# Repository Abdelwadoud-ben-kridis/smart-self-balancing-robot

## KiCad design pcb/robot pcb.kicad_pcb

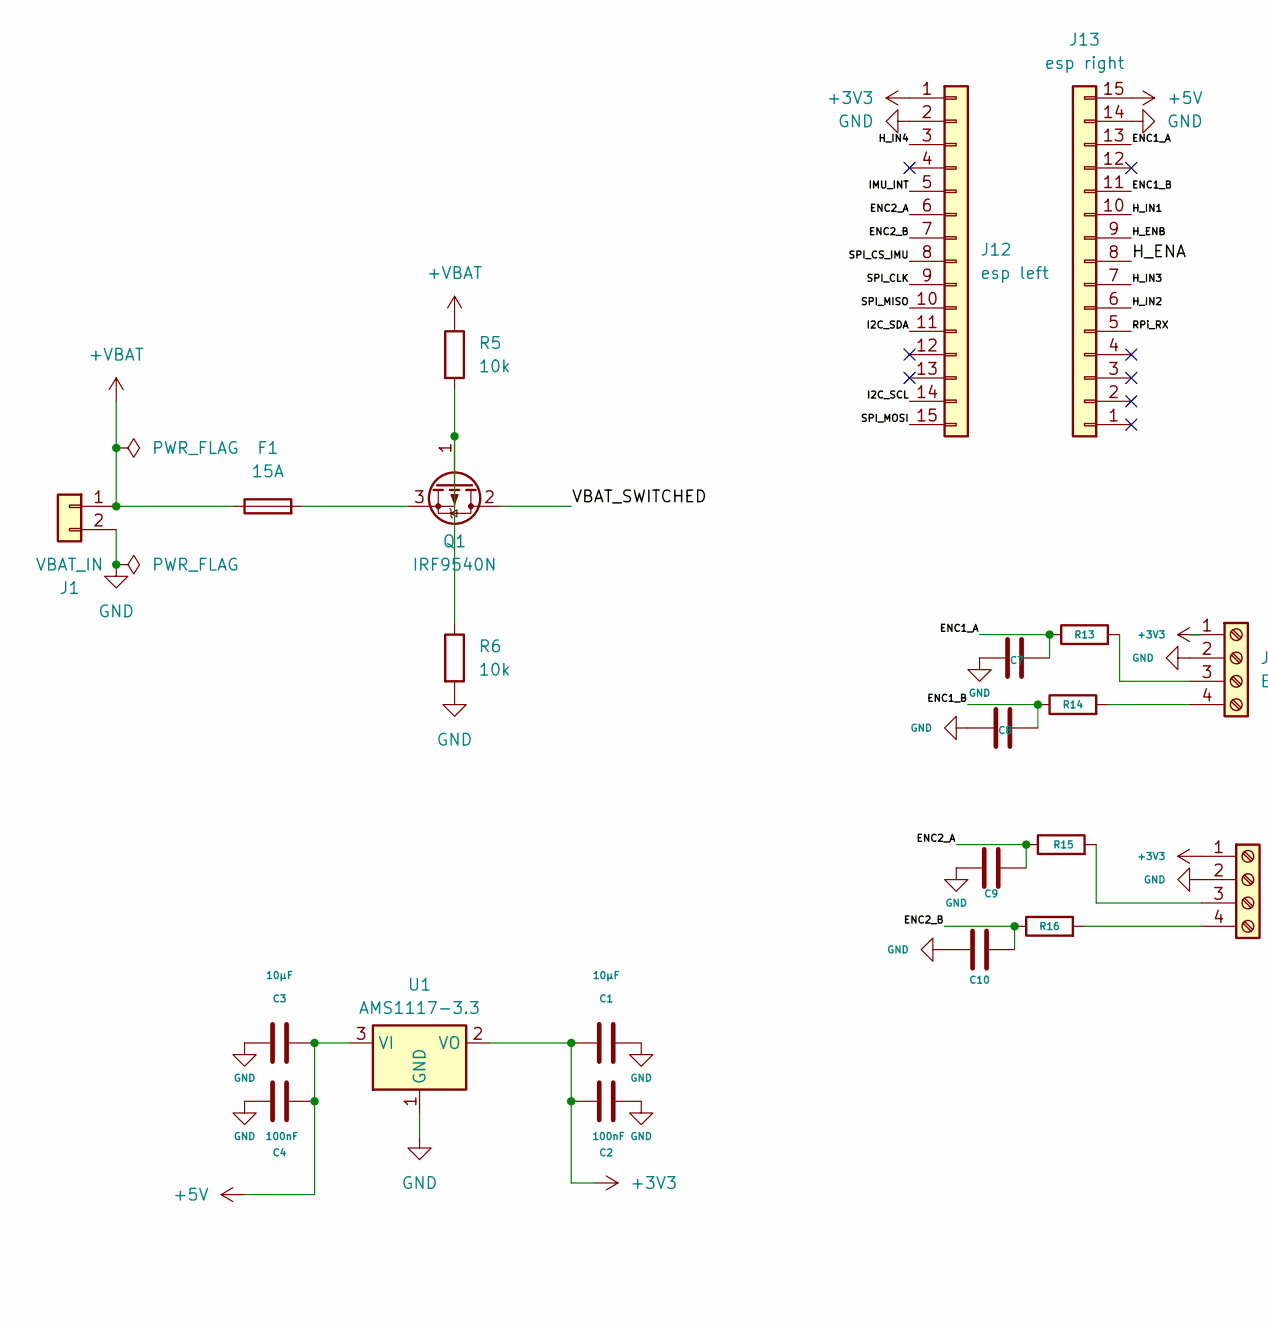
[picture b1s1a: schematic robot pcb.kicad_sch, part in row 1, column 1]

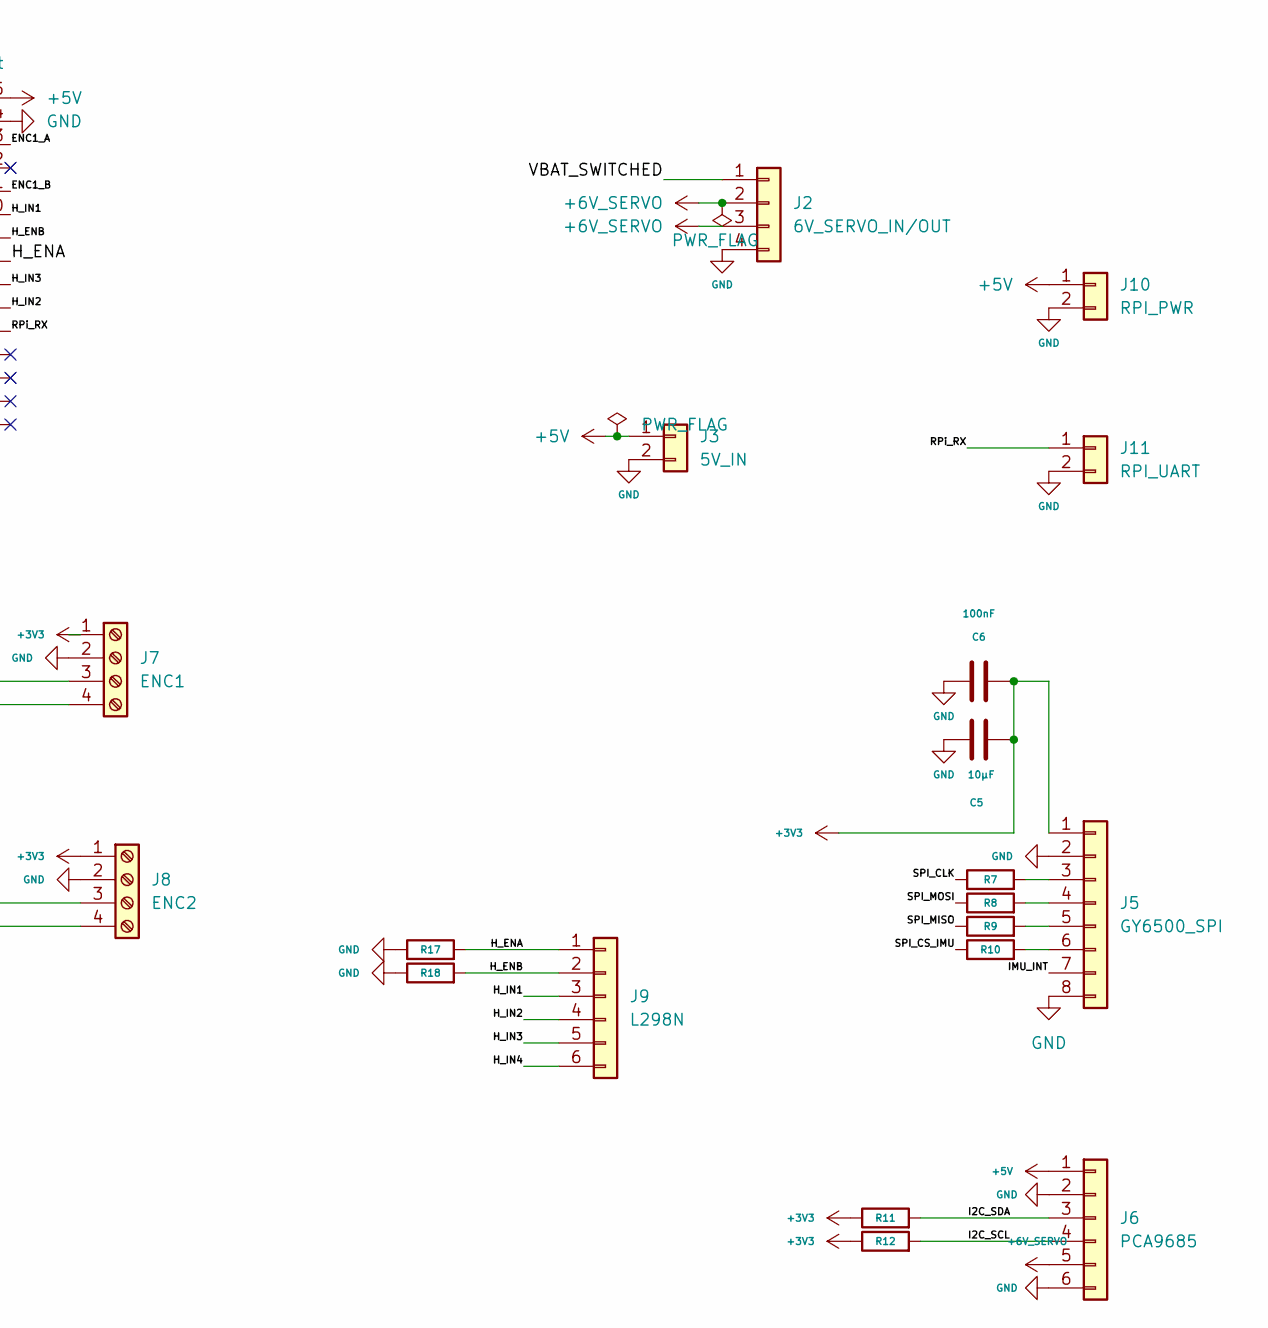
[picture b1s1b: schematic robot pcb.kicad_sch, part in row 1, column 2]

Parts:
C1, C3, C5: 10µF; CP_Radial_D5.0mm_P2.50mm
C2, C4, C6: 100nF; C_Disc_D3.8mm_W2.6mm_P2.50mm
C7, C8, C9, C10: C; C_Disc_D3.8mm_W2.6mm_P2.50mm
F1: 15A; Fuseholder_Cylinder-5x20mm_Schurter_FPG4_Vertical_Closed
J1: VBAT_IN; PinHeader_1x02_P2.54mm_Vertical
J2: 6V_SERVO_IN/OUT; PinHeader_1x04_P2.54mm_Vertical
J3: 5V_IN; PinHeader_1x02_P2.54mm_Vertical
J5: GY6500_SPI; PinHeader_1x08_P2.54mm_Vertical
J6: PCA9685; PinHeader_1x06_P2.54mm_Vertical
J7: ENC1; TerminalBlock_MaiXu_MX126-5.0-04P_1x04_P5.00mm
J8: ENC2; TerminalBlock_MaiXu_MX126-5.0-04P_1x04_P5.00mm
J9: L298N; PinHeader_1x06_P2.54mm_Vertical
J10: RPI_PWR; PinHeader_1x02_P2.54mm_Vertical
J11: RPI_UART; PinHeader_1x02_P2.54mm_Vertical
J12: esp left; PinSocket_1x15_P2.54mm_Vertical
J13: esp right; PinSocket_1x15_P2.54mm_Vertical
Q1: IRF9540N; TO-220-3_Vertical
R5, R6: 10k; R_Axial_DIN0207_L6.3mm_D2.5mm_P10.16mm_Horizontal
R7, R8, R9, R10: 33; R_Axial_DIN0207_L6.3mm_D2.5mm_P10.16mm_Horizontal
R11, R12: 4.7k; R_Axial_DIN0207_L6.3mm_D2.5mm_P10.16mm_Horizontal
R13, R14, R15, R16: 1k; R_Axial_DIN0207_L6.3mm_D2.5mm_P10.16mm_Horizontal
R17, R18: 10kΩ; R_Axial_DIN0207_L6.3mm_D2.5mm_P10.16mm_Horizontal
U1: AMS1117-3.3; SOT-223-3_TabPin2

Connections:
+3V3: C1.2, C2.2, C5.1, C6.1, J5.1, J7.1, J8.1, J12.1, R11.1, R12.1, U1.2 (VO)
+5V: C3.1, C4.1, J3.1, J6.1, J10.1, J13.15, U1.3 (VI)
+6V_SERVO: J2.2, J2.3, J6.5
+VBAT: F1.1, J1.1, R5.1
/ENC1_A: C7.2, J13.13, R13.1
/ENC1_B: C8.2, J13.11, R14.1
/ENC2_A: C9.2, J12.6, R15.1
/ENC2_B: C10.2, J12.7, R16.1
/H_ENA: J9.1, J13.8, R17.2
/H_ENB: J9.2, J13.9, R18.2
/H_IN1: J9.3, J13.10
/H_IN2: J9.4, J13.6
/H_IN3: J9.5, J13.7
/H_IN4: J9.6, J12.3
/I2C_SCL: J6.4, J12.14, R12.2
/I2C_SDA: J6.3, J12.11, R11.2
/IMU_INT: J5.7, J12.5
/RPi_RX: J11.1, J13.5
/SPI_CLK: J12.9, R7.1
/SPI_CS_IMU: J12.8, R10.1
/SPI_MISO: J12.10, R9.1
/SPI_MOSI: J12.15, R8.1
/VBAT_SWITCHED: J2.1, Q1.2 (D)
GND: C1.1, C2.1, C3.2, C4.2, C5.2, C6.2, C7.1, C8.1, C9.1, C10.1, J1.2, J2.4, J3.2, J5.2, J5.8, J6.2, J6.6, J7.2, J8.2, J10.2, J11.2, J12.2, J13.14, R6.2, R17.1, R18.1, U1.1 (GND)
unnamed: J5.3, R7.2
unnamed: J5.4, R8.2
unnamed: J5.5, R9.2
unnamed: J5.6, R10.2
unnamed: J7.3, R13.2
unnamed: J7.4, R14.2
unnamed: J8.3, R15.2
unnamed: J8.4, R16.2
unnamed: Q1.1 (G), R5.2, R6.1
unnamed: F1.2, Q1.3 (S)

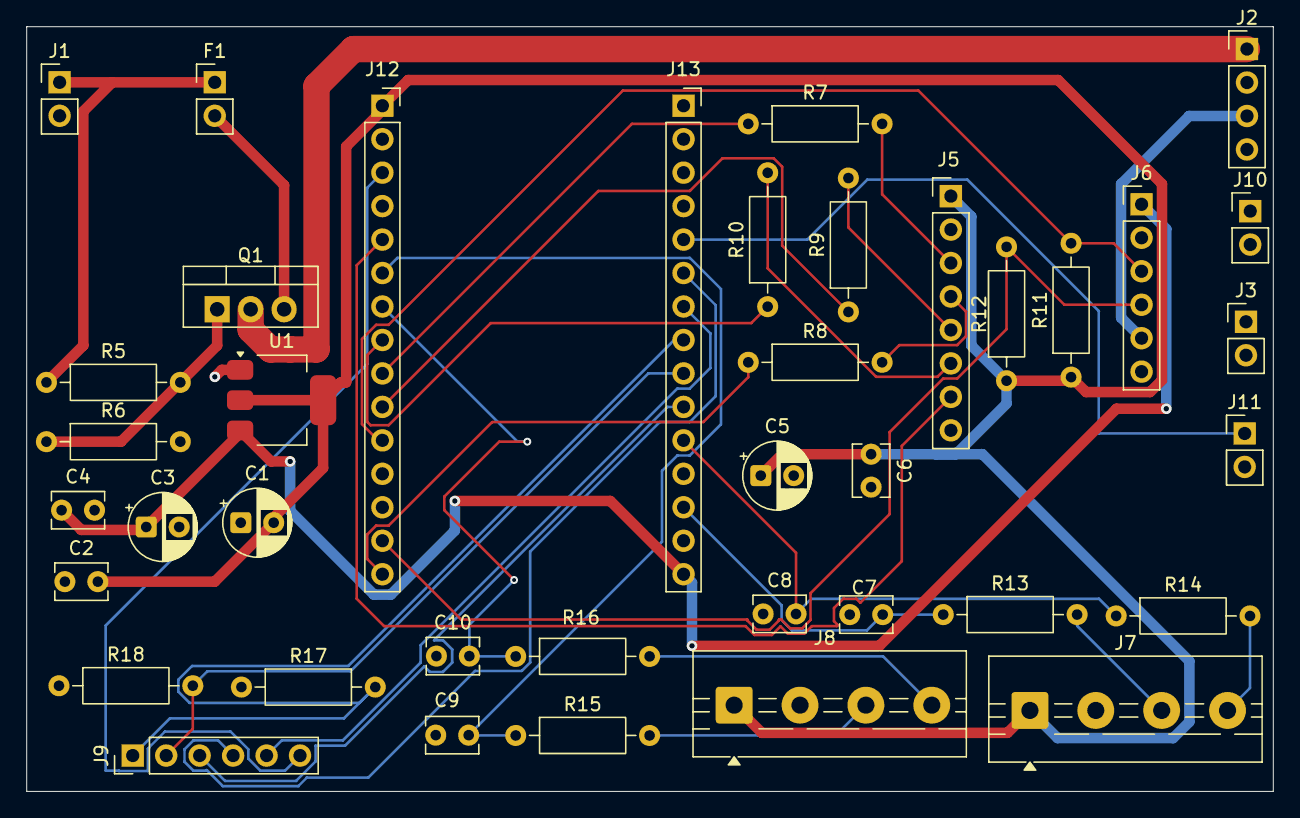
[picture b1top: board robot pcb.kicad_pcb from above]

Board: 4 copper layers, 94.6 x 58.1 mm, 39 parts (0 on the bottom side), 34 nets.

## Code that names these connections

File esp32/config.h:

#ifndef CONFIG_H
#define CONFIG_H

#include <Arduino.h>

// ── Pin map: verified Rev C distribution PCB (robot_pcb) ───────────
// ESP32 DevKit plugs into PCB sockets J12/J13. Do not change pins
// without changing the PCB.

// ── I2C (PCA9685 servo driver only) ─────────────────────────────────
#define PIN_SDA             21
#define PIN_SCL             22

// ── MPU-6500 IMU — GY-6500 module on PCB J5, SPI mode ───────────────
#define PIN_IMU_CS           5      // /SPI_CS_IMU (idle HIGH)
#define PIN_IMU_CLK         18      // /SPI_CLK
#define PIN_IMU_MISO        19      // /SPI_MISO
#define PIN_IMU_MOSI        23      // /SPI_MOSI
#define PIN_IMU_INT          4      // /IMU_INT (unused for now, polled @ 100 Hz)
#define IMU_SPI_HZ          1000000 // 1 MHz — safe for all MPU-6500 registers
#define IMU_WHO_AM_I_VAL    0x70    // MPU-6500
#define COMP_FILTER_ALPHA   0.98f   // 98 % gyro, 2 % accel
#define GYRO_LSB_PER_DPS    65.5f   // ±500 dps full scale
#define GYRO_CAL_SAMPLES    500     // bias calibration at boot (robot must be still)

// ── PCA9685 servo driver ────────────────────────────────────────────
#define PCA9685_ADDR        0x40
#define PCA9685_FREQ        50      // Hz — standard servo PWM

// Channel map per WIRING.md Rev C (CH0/1 = knees, CH2/3 = hips)
#define SERVO_CH_KNEE_L     0
#define SERVO_CH_KNEE_R     1
#define SERVO_CH_HIP_L      2
#define SERVO_CH_HIP_R      3

#define SERVO_MIN_US        500     // 0.5 ms pulse = 0°
#define SERVO_MAX_US        2500    // 2.5 ms pulse = 180°
// Hard clamp — MG996R clones jam/stall outside this window. Verify the
// real mechanical endpoints with the robot unloaded before widening.
#define SERVO_SAFE_MIN_US   600
#define SERVO_SAFE_MAX_US   2400

// ── Stance angles (degrees) ─────────────────────────────────────────
#define SIT_HIP_ANGLE       160
#define SIT_KNEE_ANGLE      20
#define STAND_HIP_ANGLE     90
#define STAND_KNEE_ANGLE    90

// ── Stand-up sequence ───────────────────────────────────────────────
#define STANDUP_STEPS       200
#define STANDUP_STEP_MS     10      // 200 × 10 ms = 2 s total
#define PID_ENABLE_STEP     100     // PID on at 50 % of sequence

// ── TB6612FNG motor driver (via PCB J9) ─────────────────────────────
// VM = 11.1 V direct, VCC + STBY tied to +3V3 on the module.
#define PIN_PWMA            25      // left motor PWM      (/H_ENA → PWMA)
#define PIN_AIN1            27      // left motor dir A    (/H_IN1 → AIN1)
#define PIN_AIN2            32      // left motor dir B    (/H_IN2 → AIN2)
#define PIN_PWMB            26      // right motor PWM     (/H_ENB → PWMB)
#define PIN_BIN1            33      // right motor dir A   (/H_IN3 → BIN1)
#define PIN_BIN2            15      // right motor dir B   (/H_IN4 → BIN2) ⚠ HIGH at boot

#define MOTOR_PWM_FREQ      1000    // Hz
#define MOTOR_PWM_RES       8       // bits → 0-255
#define MOTOR_MAX_PWM       255

// ── Wheel encoders (JGB37-520 hall quadrature, via PCB J7/J8) ───────
#define PIN_ENC1_A          13      // left  encoder Ch A
#define PIN_ENC1_B          14      // left  encoder Ch B
#define PIN_ENC2_A          16      // right encoder Ch A
#define PIN_ENC2_B          17      // right encoder Ch B

// ── UART from Raspberry Pi 5 (Serial2) ──────────────────────────────
// Rev C harness is ONE-WAY: Pi TX → PCB J11 → GPIO35 (input-only).
// No telemetry wire exists yet — set PIN_UART_TX to a free GPIO once
// an ESP32→Pi wire is added; -1 leaves TX unassigned.
#define PIN_UART_RX         35
#define PIN_UART_TX         (-1)
#define UART_BAUD           115200
#define TELEM_INTERVAL_MS   50      // 20 Hz telemetry (USB serial)

// ── PID defaults ────────────────────────────────────────────────────
#define DEFAULT_KP          25.0f
#define DEFAULT_KI           1.0f
#define DEFAULT_KD           1.5f
#define PID_OUTPUT_MIN      -255
#define PID_OUTPUT_MAX       255
#define BALANCE_ANGLE        0.0f   // target pitch (vertical)
#define D_FILTER_ALPHA       0.7f   // low-pass on derivative term

// ── Timing ──────────────────────────────────────────────────────────
#define LOOP_INTERVAL_US    10000   // 10 ms = 100 Hz

// ── Safety ──────────────────────────────────────────────────────────
#define FALL_ANGLE_THRESH   45.0f   // |pitch| > 45° → SIT

// ── Status LED ──────────────────────────────────────────────────────
#define PIN_LED              2

// ── Robot state ─────────────────────────────────────────────────────
enum RobotState {
    STATE_SIT,
    STATE_STANDING,
    STATE_BALANCE
};

#endif // CONFIG_H

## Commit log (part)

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2026-05-26 Create PCB Bill of Materials for robot project
    Added PCB Bill of Materials for self-balancing articulated leg robot, detailing project overview, power rails, and components.
2026-05-27 Update pcbBOM
2026-06-02 Rename robot pcb.kicad_pcb to pcb_files/robot pcb.kicad_pcb
2026-06-02 Add website with GitHub Pages deployment
    - index.html with 3D/Photo toggle button and no custom cursor
    - robot.glb for the 3D model viewer
    - GitHub Pages workflow
2026-06-02 Consolidate all PCB files into pcb/ folder
    Moved kicad_pro, kicad_sch, kicad_pcb, kicad_prl, and BOM into pcb/.
    Removed empty pcb_files/a.md placeholder.
    Backups stored locally in pcb/backups/ (gitignored).
2026-06-02 Add 3D model files (STEP, F3Z, STL)
2026-06-02 Rename 3d/expansion board esp 32 shield CAD.STEP to robot
2026-06-02 Rename robot to 3d/robot.STEP
2026-06-02 Add PCB Showcase, 3D Models, and Behind the Design sections
    - PCB section: component explorer, board specs, download links, signal flow diagram
    - 3D Models: interactive STL viewer with Three.js, model cards, assembly stats
    - Behind the Design: 4 engineering decision cards explaining key choices
    - Updated navigation, footer, and scroll tracking for all new sections
2026-06-02 Fix PCB specs to match Rev C BOM
    - Board: 94.6x58.1mm (not 100x80)
    - Rev C (not Rev A)
    - 1oz all layers (not 1oz/0.5oz)
    - Correct stackup: F.Signal/GND/Power/B.Signal
    - Add power trace widths, DRC status
    - Fix component descriptions (XL4016 bucks, IRF9540N protection)
2026-06-02 Fix PCB component explorer to match actual BOM Rev C
    - Split into On-Board (40 components) and External Modules sections
    - On-board: IRF9540N, AMS1117, ESP32 sockets, J9 L298N control,
    GY-6500 socket, PCA9685 socket, encoder RC filters, passives
    - External: ESP32, L298N, GY-6500/MPU-6500, PCA9685, XL4016 bucks, Pi 5
    - Removed fake VL53L0X/MPU-9250 entries (not on this PCB)
    - All descriptions match pcbBOM Rev C pinouts and notes
2026-06-02 Visual redesign: layout rhythm, typography, animations, color
    - Full-bleed cinematic moments (PCB hero, 3D viewer, gallery)
    - Section color identity (green PCB, amber power, purple models)
    - Typography scale variation (XL titles, quiet titles, pull quotes)
    - 3 cinematic stat dividers between major sections
    - New scroll animations: slide-left/right, scale-up, stagger
    - PCB: terminal-style spec table, colored component borders
2026-06-02 Trim all section descriptions to punchy one-liners
2026-06-02 Strip AI aesthetic → raw engineering notebook
    - Near-monochrome palette, single accent color (#d97757)
    - Kill Fraunces, use Inter everywhere, tighter 14px body
    - 960px max-width, 64px section padding
    - Remove all decorative elements: corner marks, canvas bg,
    gradient glows, glassmorphism, pulsing dots, spec pills
    - Remove all scroll animations (content just exists)
2026-06-02 Redesign nav and warm up background
    - Nav: clean horizontal bar with brand left, links center, status right
    Dropped section numbers, reduced to 9 key links, normal case
    Subtle backdrop blur, active link in accent color
    - Background: #161616 (warm neutral) replaces #111318 (cold blue)
    - Selection/scrollbar colors aligned to accent
    - Scroll progress bar uses accent not cyan
2026-06-02 Fix layout: wider container, single-column flow, breathing room
    - 1080px max-width (was 960, too cramped for grids)
    - Section padding 80px with subtle divider lines between
    - Hero: auto height instead of 100vh, less cramped
    - Pillars: 2 columns instead of 4 tiny ones
    - Mech/Elec grids: single column, content stacks vertically
    - Spec table values: 14px (was 17px, too loud)
2026-06-11 Revise PCB BOM for Revision C with corrections
    Updated PCB Bill of Materials for Revision C, including corrections to component values, descriptions, and connector specifications. Fixed J6.P5 connection to +6V_SERVO and updated high-current conne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
